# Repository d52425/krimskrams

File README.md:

# 雑貨（Krimskrams）

小物基板や実験データの寄せ集めリポジトリ。
ドイツ語で雑貨・がらくたの寄せ集めは **Krimskrams**（クリムスクラムス）。

## pcb/

KiCad 10 で設計した基板データ。

| 基板 | 内容 | 状態 |
|---|---|---|
| `pcb/IR_ring_strobe_driver/` | 天網ノード用 IR リング（秋月 FRS5CC, 850nm）のストロボドライバ。12V ラインを MOSFET でローサイドスイッチ、バルク 1000µF＋10µF | DRC 違反0（KiCad 10.0.8） |
| `pcb/TPS613221A_1cell_3V3_boost/` | 単セル（単3/単4）→ 3.3V 昇圧（TPS613221A）。電源スイッチは SJ1 ハンダジャンパ | DRC 違反0（KiCad 10.0.8、未接続1件は SJ1 開放分で仕様どおり） |

各基板フォルダに回路図・基板データ、生成スクリプト（`build_design.py`）、ガーバー、プレビュー、DRC レポートが入っている。

※ 基板の発注はまだ行っていない。

## models/

Blender 5.2 LTS で作る 3D モデル（画像から 3D 化したものを含む）。詳細は `models/README.md`。

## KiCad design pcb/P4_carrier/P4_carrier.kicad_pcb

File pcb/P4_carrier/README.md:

# P4 キャリア基板（ESP32-P4-POE-ETH / 32088 用）

Waveshare ESP32-P4-POE-ETH（SKU 32088）を載せるキャリア基板。ノード1台分の電源まわりと IR リングのストロボ駆動をこの1枚に集約する。

- 基板サイズ：**86 × 63 mm**、2層（**32088 は基板の南側（下辺）に配置**し、電源まわりは北側に集約。四隅のネジ穴がモジュールと干渉しない配置）
- 電源の流れ：32088 の 5V → ポリヒューズ → 入力バルク → **AE-LMR62421 昇圧モジュール（30×30mm、別基板を上に載せる）** → 12V → バルク → MOSFET ローサイドスイッチ → ネジ端子台（TB111）でリングへ
- ストロボ信号：32088 の **GPIO5（ヘッダ物理ピン10）** から取る
- 設計・検証：KiCad 10.0.8、DRC 0 violations / 0 unconnected（`drc_cli.rpt`）
- **未発注**（ガーバーは `gerber/` に生成済み）

## 32088 の載せ方（重要）

- J8 は 2×20 のメスソケット。モジュールの **RJ45 側を基板の左端** に向けて、基板の南辺に沿って差す（基板シルクの外形線と「ESP32-P4-POE-ETH」の表示が目安、ピン1ドットは RJ45 側・北列（基板中央側の列）の先頭）。
- このモジュールのヘッダは **列ごとに連番**（左列 1–20、右列 21–40、RJ45 側が若い番号）。通常の 2×20（交互配置）とは番号が違うので、J8 は物理ピン番号に合わせた専用フットプリントにしてある。
- キャリア上面図で、北列（中央側）が物理ピン 1→20（左→右）、南列（基板端側）が 21→40（左→右）。
- 5V の取り出し：物理ピン **40 = VBUS**、39 = VSYS、36 = 3V3。GND は 3/8/13/18/23/28/33/38。公式回路図のネット名では **40 = VCC1_5V、39 = VCC_5V**（下記 SJ1 の項参照）。

## SJ1（5V 選択ジャンパ）

- 1×3 ピンヘッダ（2.54mm、横向き）＋ショートキャップ。**32088 の南側、ピン39/40 の真下** に配置（VBUS/VSYS の配線は数 mm で済む）。中央が負荷側、右が VBUS（pin40）、左が VSYS（pin39）。キャップの差し位置で切り替える（実機検証で両レールを測り比べられる）。
- 公式回路図で確認した実態：**pin40 = VCC1_5V**、**pin39 = VCC_5V**。
- VCC1_5V は、PoE モジュールの 5V 出力（H7 ピン5）と Type-C の USB0_5V → Q2（AO3401）の両方が合流するノード。**PoE でも USB でも 5.0V が立つ。**
- VCC_5V（pin39）は、VCC1_5V から D2（MBR230 ショットキー）を通った後のメイン レールで、ダイオードの Vf 分（約 0.3〜0.45V）だけ低い。
- **デフォルトはキャップを右側（1-2、VBUS = VCC1_5V）** に差す（フル 5.0V が取れる側）。VSYS 側は約 4.6V になるため通常は使わない。
- キャップを差さないと昇圧側は無給電になる（32088 本体は自前の PoE/USB で動くので、止まるのはリング側だけ＝安全側の失敗になる）。

## 昇圧モジュール（AE-LMR62421）の載せ方

- 基板北西のシルク枠（30×30mm）の中に、モジュールの取付穴 **A（Ø3.0、24×24mm ピッチ、四隅 3mm 入り）** に合わせて M3 スタンドオフで固定する。スタンドオフ高さはモジュール裏面部品を避けて 6mm 以上。左上の穴（H1）はキャリアの四隅固定穴と共有で、他の隅穴と整列している。
- **端子台は付けない。メザニン直結**：モジュールの CN1/CN2 の穴（Ø1.3）の真下にキャリア側の穴（J3/J4、Ø1.5）が開いており、Ø1.2mm のピンを両方の基板に通してはんだ付けする。リード線配線が不要になり、端子台の高さ（約10mm）も消える。
- **モジュールの脚の逃げ穴（LH1）**：モジュールに実装する電解コンデンサ2本と VR1（可変抵抗）の脚が裏面に突き出す位置（メーカー寸法図から実測）に合わせ、キャリア側に Ø1.8mm の逃げ穴を7つ開けてある。**はんだ付けはしない**（メッキなし・ネットなしのただの穴）。穴の縁から GND ベタまで 1.0mm のクリアランスを両層に確保してある（実測：穴中心から 2.0mm 以内は無銅）ので、脚が GND に触れてショートすることはない。脚を長めに残した場合やスタンドオフを低くした場合の干渉逃げとして使う。
- **モジュールの向き**：電解コンデンサのある側を 32088 側（シルク枠の南辺、シルク「CAP SIDE」の側）に向ける。モジュール図面から **180° 回した向き** で、IN（CN1）が左、OUT（CN2）が右に来る。極性はマニュアルの配線図で確認済み（モジュール図面で上の穴が＋）。180° 回すのでキャリア上面から見ると **J3/J4 とも下の穴が＋（J3 = +5V、J4 = +12V）、上が GND**。
- 組み立て順：キャリアの J3/J4 にピンを差す → モジュールをスタンドオフに載せてねじ止め → モジュール上面でピンをはんだ付け → キャリア裏面でもはんだ付け。ピン長は約12mm（スタンドオフ 6mm 前提）。モジュール交換時はピン4本のはんだを外す必要がある。
- モジュール側の出力設定は **12.0V**（VR1 を 18kΩ 固定に換装した場合はそのまま。未換装ならボリュームで 12.0V に合わせ、リングを繋ぐ前に TP2 で確認）。
- 12V ラインの想定上限は **最大 18V**（基板にシルク表示あり）。リング FRS5CC の仕様上限は 15V で、18V は短パルス前提のオーバードライブ上限。

## BOM

| Ref | 部品 | 備考 |
|---|---|---|
| J8 | ピンソケット（低メス）1×20 ×2本 秋月 C-03138（2212S-20SG-36、高さ約3.5mm） | 32088 のピンヘッダを受ける（2列は 17.78mm 間隔なので一体型 2×20 は不可、1×20 を2本使う） |
| SJ1 | 1×3 ピンヘッダ 2.54mm ＋ ショートキャップ | 右側（1-2）= VBUS がデフォルト |
| F1 | ポリヒューズ MF-RX110/72-0（保持 1.1A／トリップ 2.2A／72V、秋月 113585）リードピッチ 5.1mm を基板 5.0mm ピッチに実装 | 5V 入力保護 |
| C3 | 電解 470µF/16V、Ø8、ピッチ 3.5mm | 昇圧入力バルク |
| J3/J4 | メザニンピン Ø1.2mm ×4（長さ約12mm、真鍮ピンまたは 1.2mm 単線） | 昇圧モジュールの CN1/CN2 穴へ直結（基板側は Ø1.5 スルーホール） |
| C1 | 電解 1000µF/25V、Ø10、ピッチ 5.0mm（**Rubycon PX、秋月 [117885]**） | パルス電流の供給源 |
| C2 | リード付き MLCC 10µF、X5R/X7R、**25V**、ピッチ 2.5mm | C1 の高周波側並列 |
| Q1 | SOT-23 Nch MOSFET（試作 MTN2306AN3／本番 AO3400A／代替 IRLML6344TRPBF） | 30V 級、Vgs=2.5V で Rds(on) 規定のあるもの |
| R1 | 100Ω 1/4W アキシャル | ゲート直列 |
| R2 | 10kΩ 1/4W アキシャル | ゲートプルダウン |
| R3 | 1kΩ 1/4W アキシャル | パイロット LED 制限抵抗 |
| D1 | LED 3mm（色任意） | 12V パイロット（昇圧の最小負荷も兼ねる） |
| J2 | 端子台 TB111-2-2-U-1-1（5.08mm、2P、ネジ式。昇圧モジュールの CN と同部品） | リング出力。ピン1 = R+（+12V）、ピン2 = R−（FET ドレイン）。リングのリード線を直接ネジ止め（圧着不要） |
| H1–H4 | M3 スタンドオフ＋ねじ | 昇圧モジュール固定（基板側は Ø3.2 貫通穴）。**H1（左上）はキャリアの固定と共有**（裏からシャーシへ止めるネジで共締めする） |
| H5–H7 | M3 ねじ | キャリアの四隅固定穴（右上＋下辺の左右）。左上は H1 と共有。四隅は長方形に整列し（左列 x=4／右列 x=82／上行 y=−1／下行 y=54）、モジュールと干渉しない |

## テストポイント

- TP1 = +5V（ポリヒューズ後段）
- TP2 = +12V（昇圧出力・リング接続前にここで電圧確認）

## 注意・未検証

- 実機の 32088 で VBUS/VSYS の実電圧と、PoE 給電時の 5V レールの余裕（P4 本体＋昇圧入力＋カメラ系）は未検証。
- 昇圧モジュールのスイッチングノイズがカメラ画像へ与える影響は実機確認待ち（共通 GND 前提）。
- モジュール（32088）自体の固定はヘッダの摩擦のみ。輸送・振動環境では別途押さえを検討。
- FRS5CC は CDS（光センサ）をバイパス済みにしておくこと（電圧がかかれば点く状態にする）。

## ファイル

- `P4_carrier.kicad_pro` から開くこと（プロジェクトローカルのライブラリテーブルを使うため）
- `custom.pretty/` … J8・SJ1・F1・J2・LH1（脚逃げ穴）・テストポイント・メザニンピン（J3/J4）の自作フットプリント
- `build_design.py` … 回路図＋基板の生成スクリプト（KiCad 同梱 python で実行）
- `gerber/` … 製造用ガーバー一式（9ファイル＋ドリル＋job）
- `preview_*` … 基板上面/下面・回路図のプレビュー

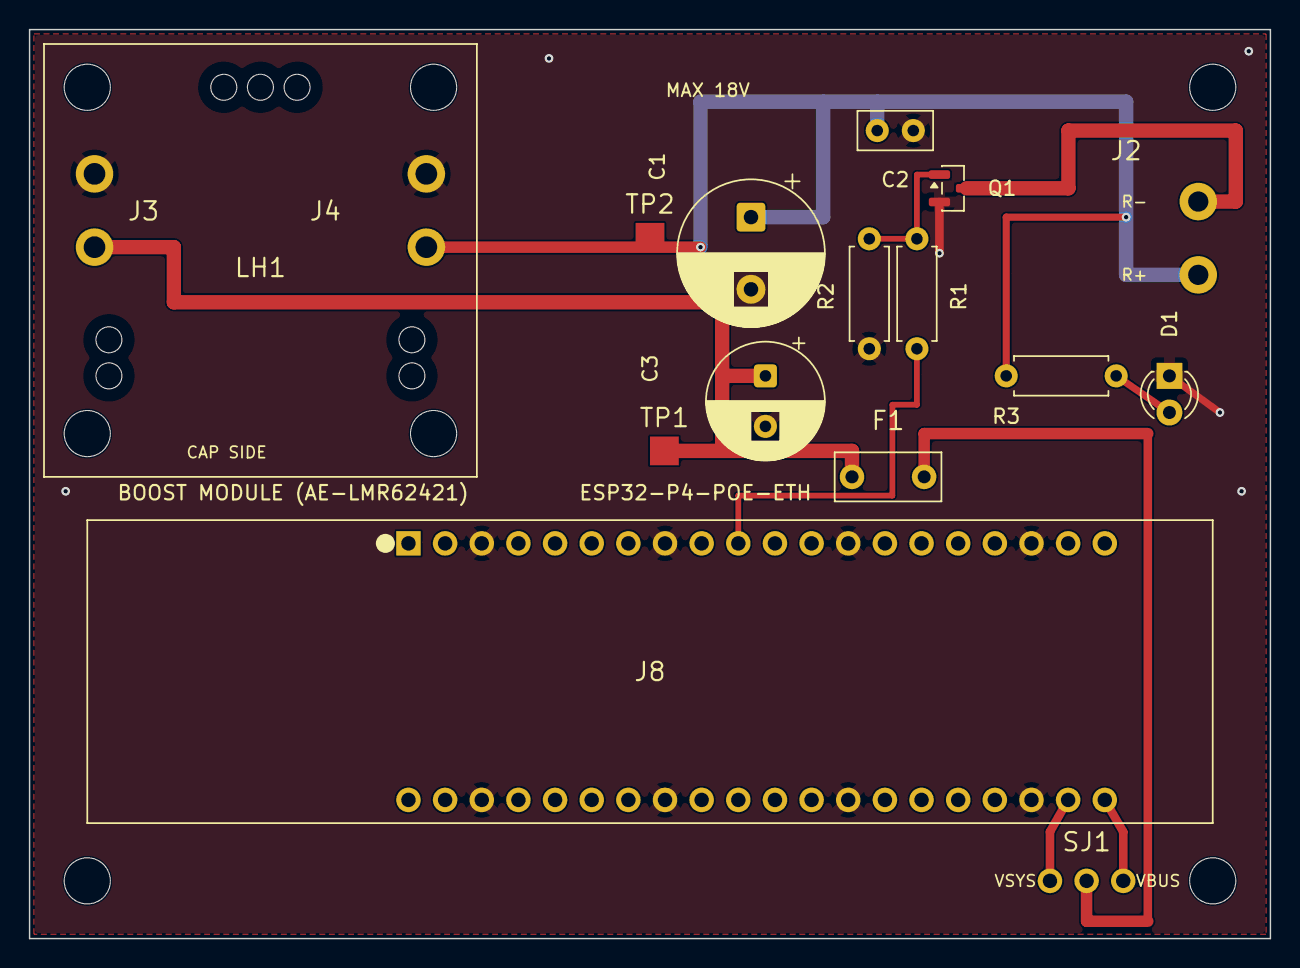
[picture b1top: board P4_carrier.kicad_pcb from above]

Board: 2 copper layers, 86.0 x 63.0 mm, 24 parts (0 on the bottom side), 10 nets.

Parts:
C1: 1000uF/25V PX; CP_Radial_D10.0mm_P5.00mm
C2: 10uF; C_Disc_D5.0mm_W2.5mm_P2.50mm
C3: 470uF/16V; CP_Radial_D8.0mm_P3.50mm
D1: 12V PILOT; LED_D3.0mm
F1: PTC 1A; PTC_P5.00mm
H1, H2, H3, H4, H5, H6, H7: MountingHole_3.2mm_M3
J2: RING OUT TB111; TB111_1x02_P5.08
J3: BOOST IN MEZZ; MZ_1x02_P5.08
J4: BOOST OUT MEZZ; MZ_1x02_P5.08
J8: ESP32-P4-POE-ETH (32088); HDR_2x20_P4
LH1: BOOST LEG CLEARANCE; LEG_CLEAR_7
Q1: MTN2306AN3/IRLML6344; SOT-23
R1: 100; R_Axial_DIN0207_L6.3mm_D2.5mm_P7.62mm_Horizontal
R2: 10k; R_Axial_DIN0207_L6.3mm_D2.5mm_P7.62mm_Horizontal
R3: 1k; R_Axial_DIN0207_L6.3mm_D2.5mm_P7.62mm_Horizontal
SJ1: 5V SEL (HDR+CAP); HDR_1x03_P2.54
TP1, TP2: TestPoint_D2.0mm

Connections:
+5V: C3.1, F1.2, J3.1, TP1.1
+5V_IN: F1.1, SJ1.2
+12V: C1.1, C2.1, J2.1, J4.1, R3.1, TP2.1
DRAIN: J2.2, Q1.3
GATE: Q1.1, R1.1, R2.1
GND: C1.2, C2.2, C3.2, D1.1, J3.2, J4.2, J8.3, J8.8, J8.13, J8.18, J8.23, J8.28, J8.33, J8.38, Q1.2, R2.2
LED_A: D1.2, R3.2
STROBE: J8.10, R1.2
VBUS: J8.40, SJ1.1
VSYS: J8.39, SJ1.3

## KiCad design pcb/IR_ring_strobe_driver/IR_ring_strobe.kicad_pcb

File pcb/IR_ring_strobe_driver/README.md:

# IRリング ストロボ駆動基板（GPIO → MOSFET 12Vパルススイッチ）

天網（ESP32-P4ノード）用。P4 の GPIO（3.3V）で Nch MOSFET を駆動し、FRS5CC IR LED リング（12V / 200mA）への 12V ラインをローサイドでパルススイッチする小基板。昇圧側は常時 ON で 12V レールを維持する前提で、本基板はバルクコンデンサとスイッチだけを持つ（キャリア基板へ統合する前の単体検証用）。

- 基板：30×30mm、2層、M2 取付穴×4（四隅）。受動部品はスルーホール実装（Q1 のみ SOT-23 面実装）。部品は C1・C2・Q1・R1・R2 を x=15mm の縦一列に配置（C1 は 90° 回転、抵抗は横向き）
- 入力 J1（ターミナルブロック 3.5mmピッチ 3極、基板左端の上下中央）：上から pin1 = +12V、pin2 = GND、pin3 = STROBE（GPIO 入力）。シルク表示「+12V / GND / STR」
- 出力 J2（ターミナルブロック 3.5mmピッチ 2極、基板右端の上下中央）：上が pin2 = リング＋（+12V）、下が pin1 = リング−（FET ドレイン）。シルク表示「R+ / R-」
- 改訂（2026-11-27）：コネクタをピンヘッダ／JST-XH からターミナルブロックへ変更（圧着不要にするため）。基板サイズ 30×30mm は不変
- 改訂（2026-11-27）：部品配置を中央の縦列（C1・C2・Q1）に変更。J2 のピン割り当てを 上=+12V / 下=ドレイン に入れ替え
- 改訂（2026-11-27）：部品を x=15mm の縦一列配置に変更（C1 は 90° 回転）。TP2 を削除し、取付穴を四隅 4 つに。OUT ブロックは上下中央に配置
- 改訂（2026-11-27）：印加電圧の上限を 18V と明記（基板シルクに「MAX 18V」表示を追加）。C2 の耐圧指定を 25V に訂正
- 印加電圧：通常 12V、最大 18V（リング FRS5CC の仕様上限は 15V。18V は短パルス前提のオーバードライブ上限）

## 回路

```
 +12V ──┬── C1 1000µF/25V ── GND
        ├── C2 10µF ──────── GND
        └── J2.2 リング＋
 J2.1 リング− ── Q1 D
 GPIO ── R1 100Ω ── Q1 G、R2 10kΩ で GND へプルダウン
 Q1 S ── GND
```

- パルス電流は C1（＋C2）から供給する。配線ループ（C1 → J2 → リング → Q1 → GND → C1）を短く配置した
- Q1 は Vgs=2.5V で Rds(on) が規定されたロジックレベル品を使うこと（3.3V 駆動で確実に飽和させるため）。Vds は 12V＋昇圧スパイクに対して 30V 級
- 負荷は LED＋抵抗で誘導性ではないためフライバックダイオードは不要
- リング側 FRS5CC は CDS をバイパス（ショート）して「12V が来れば点灯」にしておくこと
- 駆動タイミング（FW 側）：GPTimer / MCPWM 等のハードウェアタイマで、露光開始の 100µs 以上前に ON、幅＝露光＋マージン

## BOM

| Ref | 部品 | 仕様・候補 | 備考 |
|---|---|---|---|
| Q1 | Nch MOSFET SOT-23（1=G, 2=S, 3=D） | 試作：MTN2306AN3（CYStek、秋月 I-17513、30V/5.5A、Rds(on) max 37mΩ @2.5V）／ 本番：AO3400A 純正（A&O、30V/5.7A）／ 代替：IRLML6344TRPBF | 無印 AO3400 クローンは特性ばらつき大、避ける |
| R1 | 抵抗 スルーホール axial（DIN0207 型）、100Ω、1/4W | ゲート直列（発振止め＋GPIO 保護） | |
| R2 | 抵抗 スルーホール axial（DIN0207 型）、10kΩ、1/4W | ゲートプルダウン（リセット中の誤点灯防止） | |
| C1 | 電解コンデンサ ラジアル Ø10×16 級、1000µF/25V 低ESR | ピッチ 5.0mm | バルク。パルス電流の供給源 |
| C2 | リード付き積層セラミック、10µF、X5R/X7R、25V、リードピッチ 2.5mm | C1 と並列（高周波側）。レール最大 18V のため 25V 品を使うこと | |
| J1 | ターミナルブロック 3.5mmピッチ 3極、プッシュイン式 | Phoenix Contact PT 1,5/3-3,5-H 相当 | +12V / GND / STROBE 入力。配線は被覆を剥いて差し込むだけ（圧着不要） |
| J2 | ターミナルブロック 3.5mmピッチ 2極、プッシュイン式 | Phoenix Contact PT 1,5/2-3,5-H 相当 | リング出力 |

## ファイル

- `IR_ring_strobe.kicad_pro / .kicad_sch / .kicad_pcb`：KiCad 10 プロジェクト（プロジェクトローカルの lib テーブル同梱。回路図のみ旧形式で、開いて保存すると 10 形式へ移行）
- `gerber/`：ガーバー9点＋ドリル＋ジョブファイル（発注可）
- `wiring_diagram.png`：昇圧モジュール込みの全体結線図（生成元 `draw_wiring.py`）
- `preview_*.pdf / preview_pcb_top*.png`：プレビュー
- `netlist.txt`：設計意図のネット一覧
- `build_design.py`：生成スクリプト（再生成用、KiCad 同梱 Python で実行）。生成後に `kicad-cli pcb drc --refill-zones --save-board` でゾーン充填と DRC、`kicad-cli pcb export gerbers / drill` でガーバー出力

## 検証状態（2026-11-27）

- KiCad DRC：違反 0 件・未接続 0・フットプリントエラー 0
- 実機未検証：12V ラインのパルス時ドロップ、昇圧ノイズの画への影響、FET 発熱（計算上 mW 級で問題なしの見込み）

発注・購入は未実施（指示待ち）。

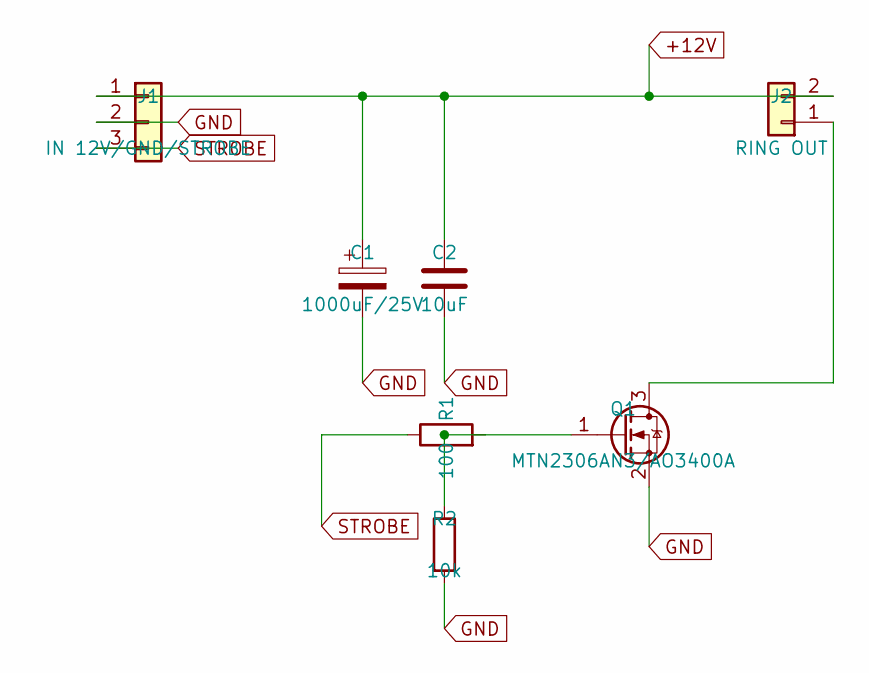
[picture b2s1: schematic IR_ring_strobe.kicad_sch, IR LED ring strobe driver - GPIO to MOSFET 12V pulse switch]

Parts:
C1: 1000uF/25V; CP_Radial_D10.0mm_P5.00mm
C2: 10uF; C_Disc_D5.0mm_W2.5mm_P2.50mm
J1: IN 12V/GND/STROBE; TerminalBlock_Phoenix_PT-1,5-3-3.5-H_1x03_P3.50mm_Horizontal
J2: RING OUT; TerminalBlock_Phoenix_PT-1,5-2-3.5-H_1x02_P3.50mm_Horizontal
Q1: MTN2306AN3/AO3400A; SOT-23
R1: 100; R_Axial_DIN0207_L6.3mm_D2.5mm_P7.62mm_Horizontal
R2: 10k; R_Axial_DIN0207_L6.3mm_D2.5mm_P7.62mm_Horizontal

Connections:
+12V: C1.1, C2.1, J1.1, J2.2
DRAIN: J2.1, Q1.3 (D)
GATE: Q1.1 (G), R1.2, R2.1
GND: C1.2, C2.2, J1.2, Q1.2 (S), R2.2
STROBE: J1.3, R1.1

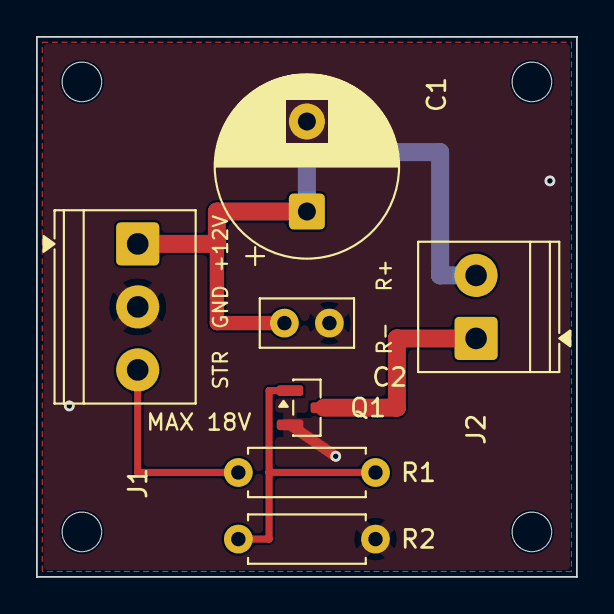
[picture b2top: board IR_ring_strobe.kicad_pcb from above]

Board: 2 copper layers, 30.0 x 30.0 mm, 11 parts (0 on the bottom side), 5 nets.

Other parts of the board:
H1, H2, H3, H4: MountingHole_2.2mm_M2

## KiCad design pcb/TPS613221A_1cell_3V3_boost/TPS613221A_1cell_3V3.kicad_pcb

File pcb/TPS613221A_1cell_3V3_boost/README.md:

# 単セル → 3.3V 昇圧基板（TPS613221A）

電池1本（単3/単4、アルカリ 1.5V / NiMH 1.2V）から 3.3V を作る昇圧基板。
専用小基板として設計（30×20mm、2層、部品は片面のみ）。

## 仕様・要点

- IC: **TPS613221A**（3.3V固定出力）。ENピンが無い常時ON構成なので、電源の入り切りは **SJ1（ハンダジャンパ）をブリッジするか**で決める。待機電流は IC の Iq 6.5µA typ が下限。
- 起動電圧 0.87V max（負荷250Ω以上時）。取り出せる電流は入力電圧で決まる：データシート試算例で 0.9V入力時 約114mA。電池終盤は 50–80mA 級が目安。
- J1（2.54mm 1×3ピンヘッダ）：**1 = BAT+ / 2 = GND / 3 = +3.3V出力**。そのままユニバーサル基板やブレッドボードに挿せるモジュール形。
- テストポイント：TP1 = BAT（SJ1の後段）、TP2 = SW波形、TP3 = +3.3V。
- 取付穴：M2 ×3（H1/H2/H3）。

## BOM

| Ref | 部品 | 備考 |
|---|---|---|
| U1 | TI TPS613221ADBVT（SOT-23-5） | DigiKey 切りテープ ¥223 税込/個（2026-11-26確認）。刻印 1N4L |
| L1 | 4.7µH Murata DFE252012P-4R7M=P2 | Isat 1.7A / DCR 165mΩ。データシート推奨インダクタ表より |
| C1 | 22µF セラミック 0805 | 入力側。電池リードのインピーダンス対策で追加（データシート回路には無い） |
| C2 | 22µF セラミック 0805 | 出力側。DCバイアスで実効容量が減るので公称22µF（実効10µF以上を確保）。例：Murata GRM21BZ71A226ME15 |
| C3 | 1µF セラミック 0603 | U1 の VOUT/GND ピン直近に配置 |
| J1 | ピンヘッダ 2.54mm 1×3 | |
| SJ1 | ハンダジャンパ（部品なし） | ブリッジで電源ON |

コンデンサは X5R/X7R、定格 6.3V 以上。

## レイアウト方針

- 電池 → L → SWピン、VOUT → C2/C3 → GND のループを最短に配置。SWノードの銅箔は最小限。
- 裏面は GND ベタ全面、表面も GND ポア（ゾーン充填済み）。GND は各所ビアでスチッチ。
- 出力（+3V3）は基板外周を回して J1 pin3 に戻す配線。

## 検証状態（2026-11-26）

- 回路図ネットリストと基板の接続が全ネット一致（BAT が SJ1 で2つに分かれるのはジャンパ仕様どおり）。
- **KiCad 10.0.8 の kicad-cli DRC（ゾーン再充填あり）で違反 0 件**（2026-11-27、`drc_cli.rpt`）。未接続として残る1件は SJ1 ハンダジャンパの開放ギャップで、仕様どおり（ブリッジで導通）。
- 実機未検証：起動波形・リップル・最大負荷は試作後にオシロで確認すること。

## 改訂履歴

- 2026-11-27：KiCad 10.0.8 で再生成し、レイアウトを最適化。DRC 違反 0 件を確認。

## ファイル

- `TPS613221A_1cell_3V3.kicad_pro / .kicad_sch / .kicad_pcb` — KiCad 10 プロジェクト（プロジェクトローカルの sym/fp-lib-table 付き。回路図は開くときに 10 形式へ移行される）
- `gerber/` — ガーバー一式＋ドリル（そのまま発注可能）
- `preview_*.pdf / preview_pcb_top_zoom.png` — プレビュー
- `build_design.py` — 回路図・基板の生成スクリプト（再生成用。KiCad 10 の python + ライブラリで実行：`KICAD_SHARE=<kicad share dir> python3 build_design.py`）
- `drc_cli.rpt` — KiCad 10.0.8 kicad-cli の DRC レポート（違反0件）
- `netlist.txt` — 検証時のネットリスト出力

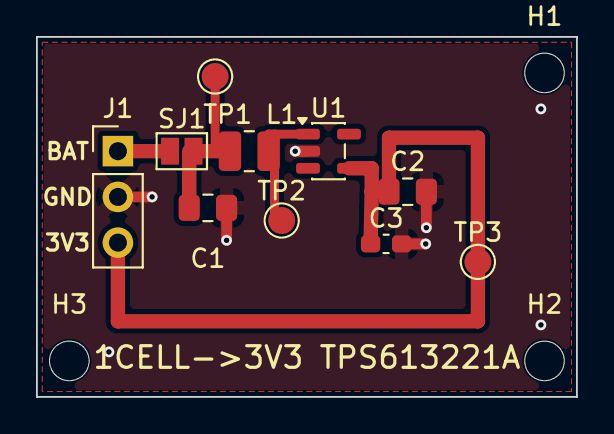
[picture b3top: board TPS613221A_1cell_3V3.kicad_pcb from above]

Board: 2 copper layers, 30.0 x 20.0 mm, 13 parts (0 on the bottom side), 4 nets.

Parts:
C1, C2: 22uF; C_0805_2012Metric_Pad1.18x1.45mm_HandSolder
C3: 1uF; C_0603_1608Metric_Pad1.08x0.95mm_HandSolder
H1, H2, H3: MountingHole_2.2mm_M2
J1: BAT/GND/+3V3; PinHeader_1x03_P2.54mm_Vertical
L1: 4.7uH DFE252012P-4R7M; L_1008_2520Metric
SJ1: BRIDGE=ON; SolderJumper-2_P1.3mm_Open_Pad1.0x1.5mm
TP1: BAT; TestPoint_Pad_D1.5mm
TP2: SW; TestPoint_Pad_D1.5mm
TP3: +3V3; TestPoint_Pad_D1.5mm
U1: TPS613221ADBVT; SOT-23-5

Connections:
+3V3: C2.1, C3.1, J1.3, TP3.1, U1.4
BAT: C1.1, J1.1, L1.1, SJ1.1, SJ1.2, TP1.1
GND: C1.2, C2.2, C3.2, J1.2, U1.2
SW: L1.2, TP2.1, U1.1

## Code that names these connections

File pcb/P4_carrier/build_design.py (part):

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The carrier plugs onto the 32088's 2x20 header (J8) and carries the
whole power chain for one Tenmou node:

    J8 pin40 VBUS / pin39 VSYS (solder-jumper select, SJ1)
      -> polyfuse F1 -> input bulk 470uF
      -> mezzanine pins into an AE-LMR62421 boost module (30x30mm,
         M3 standoffs, no terminal blocks) and back in at +12V
      -> bulk 1000uF/25V + 10uF -> Nch MOSFET low-side switch
      -> TB111 screw-terminal ring output (FRS5CC), strobe from J8 pin10

Board: 86x68mm, 2-layer. The 32088 header numbering is consecutive
per column (left column 1-20, right column 21-40, counted from the
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LED_NAMES = symbol_pin_names("Device.kicad_sym", "LED")
LED_A = [n for n, nm in LED_NAMES.items() if nm == "A"][0]
LED_K = [n for n, nm in LED_NAMES.items() if nm == "K"][0]
print("LED anode pin:", LED_A, "cathode pin:", LED_K)


PLAN = {
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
